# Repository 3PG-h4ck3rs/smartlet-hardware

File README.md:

smart-relay-hardware
====================

A single coil bistable relay controlled by the rfd22301 bluetooth module using a si9986 driver.
Schematic:
----------

Board:
----------

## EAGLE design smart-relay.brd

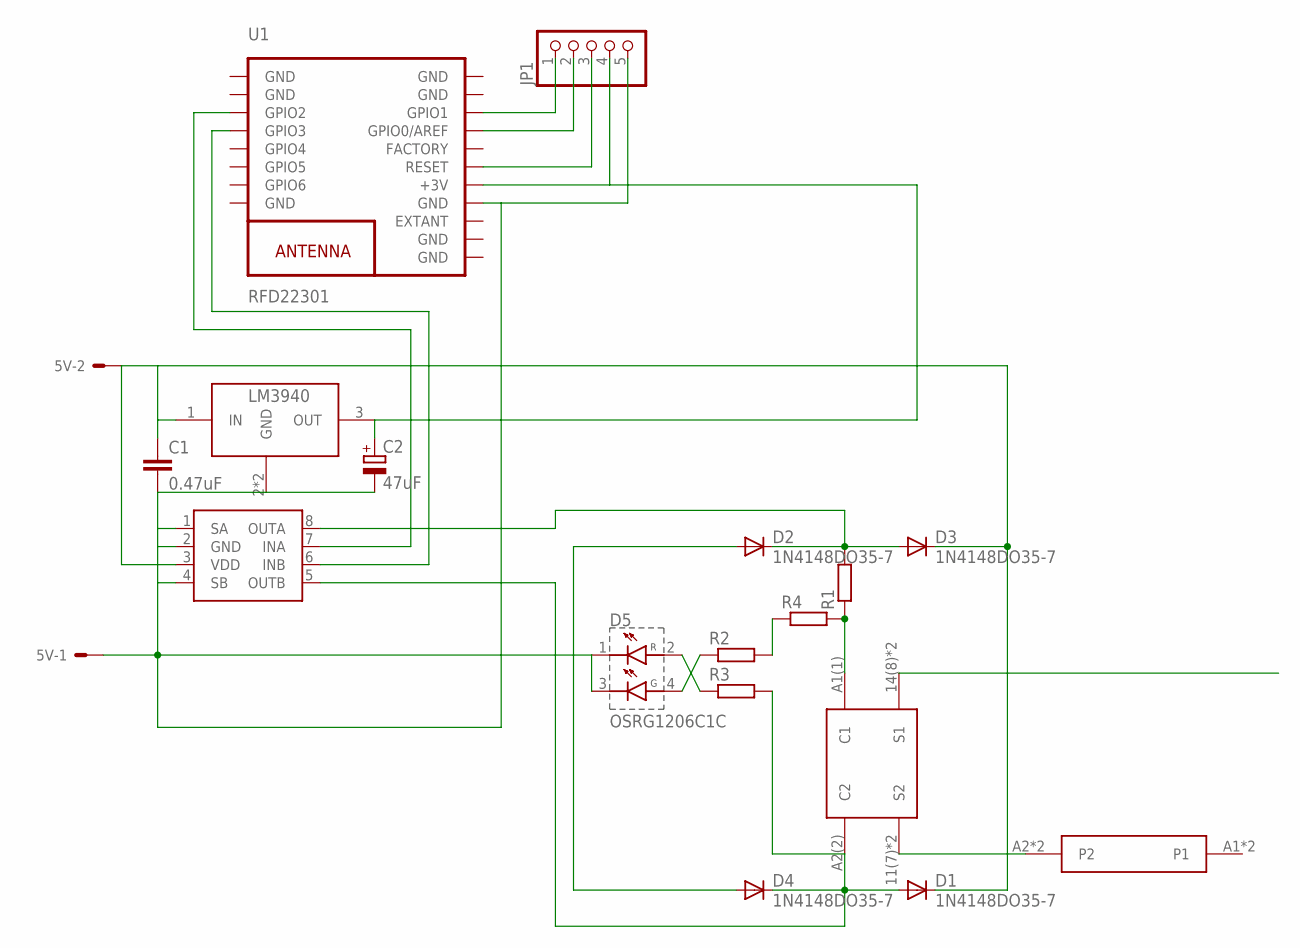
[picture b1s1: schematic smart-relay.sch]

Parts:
5V: 22-23-2021
C1: 0.47uF; C3216
C2: 47uF; CT7343
D1, D2, D3, D4: 1N4148DO35-7; DO35-7
D5: OSRG1206C1C
FUSE: KEYSTONE3562
JP1: PINHD-1X5; 1X05
LM3904: LDO3940; SOT223
R1: R-EU_0204/2V; 0204V
R2, R3: RR1206; R1206
R4: R-EU_0204/5; 0204/5
U1: RFD22301
U$1: RMB851; RMB581
U$2: SI9986SO8; SO-08

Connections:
GND: U1.1 (GND), U1.2 (GND), U1.8 (GND), U1.9 (GND), U1.10 (GND), U1.18 (GND), U1.19 (GND)
unnamed: FUSE.A2 (P2), FUSE.A2_ (P2), U$1.11(7) (S2), U$1.21(4) (S2)
unnamed: U$1.14(8) (S1), U$1.24(5) (S1)
unnamed: JP1.1, U1.17 (GPIO1)
unnamed: U1.3 (GPIO2), U$2.7 (INA)
unnamed: U1.4 (GPIO3), U$2.6 (INB)
unnamed: 5V.2, C1.1, D1.C, D3.C, LM3904.1 (IN), U$2.3 (VDD)
unnamed: 5V.1, C1.2, C2.-, D2.A, D4.A, D5.1, D5.3, JP1.5, LM3904.2 (GND), LM3904.4 (GND), U1.12 (GND), U$2.1 (SA), U$2.2 (GND), U$2.4 (SB)
unnamed: C2.+, JP1.4, LM3904.3 (OUT), U1.13 (+3V)
unnamed: D2.C, D3.A, R1.2, U$2.8 (OUTA)
unnamed: D1.A, D4.C, R3.2, U$1.A2(2) (C2), U$2.5 (OUTB)
unnamed: JP1.2, U1.16 (GPIO0/AREF)
unnamed: JP1.3, U1.14 (RESET)
unnamed: R1.1, R4.2, U$1.A1(1) (C1)
unnamed: R2.2, R4.1
unnamed: D5.4, R2.1
unnamed: D5.2, R3.1

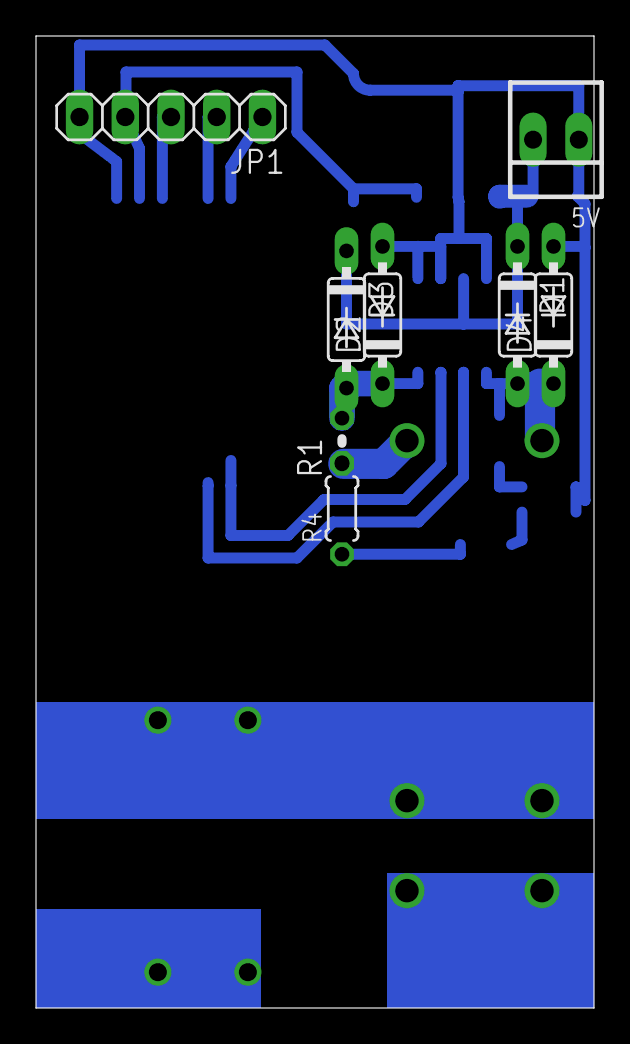
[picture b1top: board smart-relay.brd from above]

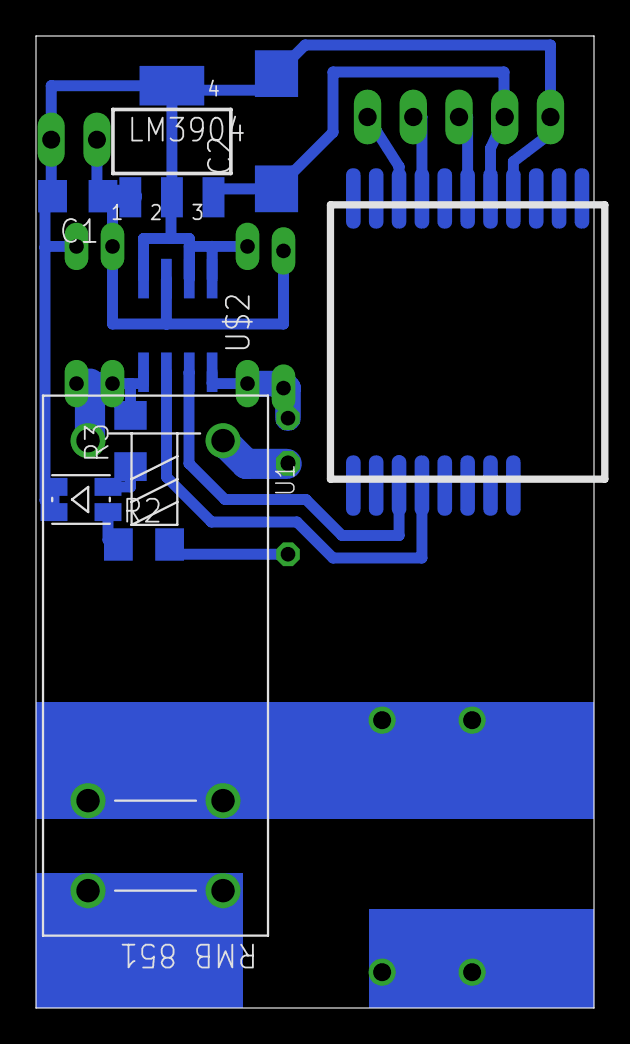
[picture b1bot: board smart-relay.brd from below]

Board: 2 copper layers, 31.0 x 54.0 mm, 18 parts (9 on the bottom side), 17 nets.

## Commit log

2014-10-16 Added LED and moved trace outside of bluetooth.
    * Added a bicolor LED in parallel with the relay coil to make debugging
    easier.
    * Moved trace from under rfd22301 place so the PCB can be cut and the
    rfd22301 can pe soldered in line with the rest of the PCB. Removing
    the rfd22301 will be easier this way.
2014-10-16 Created README.md
2014-10-16 added copper pour 2mm clearance
2014-10-16 PCB mask inverted x 3 (mirrored)
2014-11-02 Added the initial firmware
2014-11-02 Fixed hardware readme
2014-11-03 Moving firmware to different repo
